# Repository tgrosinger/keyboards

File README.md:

# Keyboards by Tony

Resources and designs for the custom keyboards I have created.

## The Keyboards

### Chrysemys

[Source Files](https://git.sr.ht/~tgrosinger/keyboards/tree/main/item/chrysemys)

A 34-key single-board keyboard created with [Ergogen](https://ergogen.xyz). Powered by a ProMicro-compatible board, such as the nice!nano.

This keyboard is my first attempt at using Ergogen, and my first custom keyboard, so it will likely be rough around the edges. I predict there will be future keyboards listed here which refine the ideas implemented in this board.

### Pseudacris

[Source Files](https://git.sr.ht/~tgrosinger/keyboards/tree/main/item/pseudacris)

A 34-key single-board keyboard created with [Ergogen](https://ergogen.xyz). Powered by an integrated MCU, derived directly from the [nRFMicro](https://github.com/joric/nrfmicro/).

This keyboard is almost identical to Chrysemys, but switches to normal Choc switches, adds hotswap, and moves the switches closer together.

### Future Keyboards

Eventually I would like to build a keyboard which has an integrated trackpoint, trackpad, or trackball. It will likely be based on Pseudacris.

## License

All files in this repository are covered by the GPLv3 license. See the [LICENSE](https://git.sr.ht/~tgrosinger/keyboards/tree/main/item/LICENSE) file for more information.

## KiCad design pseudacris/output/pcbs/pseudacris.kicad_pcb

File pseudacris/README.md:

# Pseudacris

A 34-key single-board keyboard created with [Ergogen](https://ergogen.xyz).

This keyboard is materially extremely similar to Chrysemys, with the intention to change the following:

- Change from Kailh Choc Mini to the normal Kailh Choc switches.
  - I have not been happy with how the mini switches feel to type on. They feels as though they are going to bind up too often and especially make chords more difficult.
  - This will reduce manufacturing costs because the extra cutouts needed for the mini switches requires excess milling time.
- Use hotswap sockets for the switches.
- Move the switches closer together, so there is less of a gap between key caps.
- Use an integrated MCU, based on the nRFMicro rather than a nice!nano.

## Building Firmware

The firmware for this keyboard can be found on my [ZMK fork](https://github.com/tgrosinger/zmk/tree/tgrosinger-keyboards/app/boards/arm/pseudacris). Instructions for building can be found in the readme in that directory.

If you would like to build your own key layout for this keyboard, follow the instruction for [Building from `zmk-config` folder](https://zmk.dev/docs/development/build-flash#building-from-zmk-config-folder).

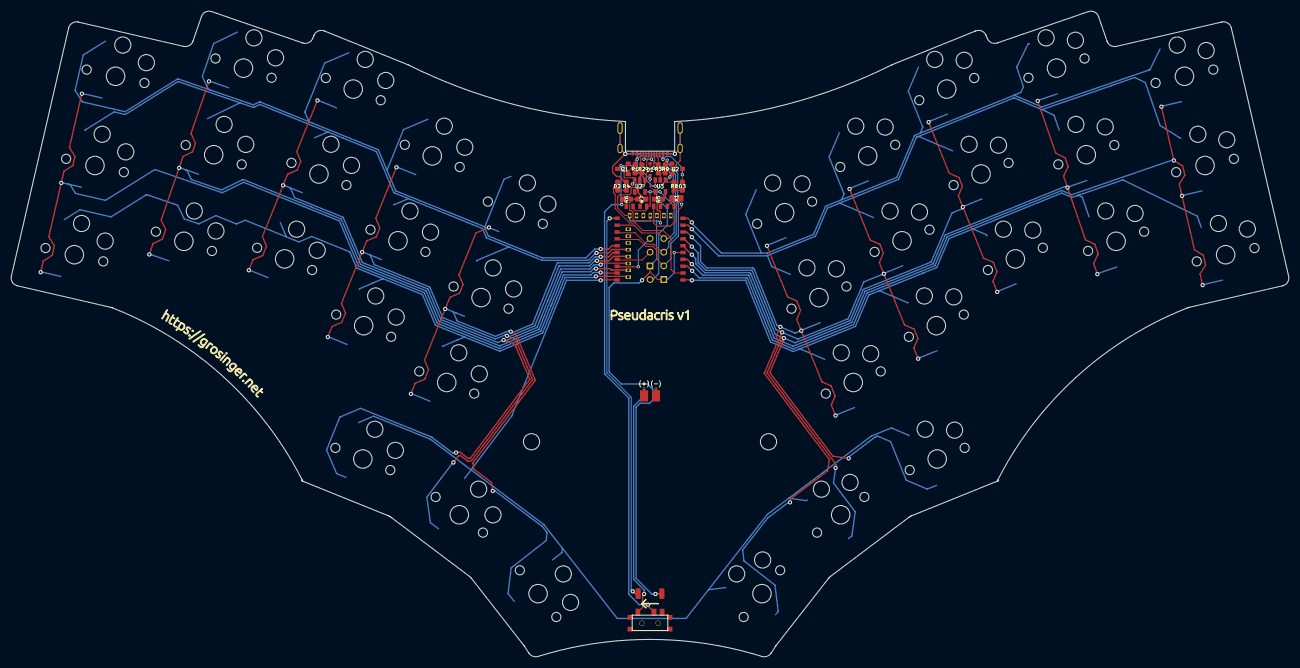
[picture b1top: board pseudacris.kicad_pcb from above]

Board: 2 copper layers, 237.2 x 119.9 mm, 60 parts (0 on the bottom side), 39 nets.

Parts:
B1: Button; TwoLeadButton
BT1: Battery_Cell; BatteryPads
D1: 1N5819; D_SOD-323F
D2: BLUE; LED_0603_1608Metric
D3: RED; LED_0603_1608Metric
J1: USB-C USB 2.0 MC-372; USB-C_C168688
J2: Conn_01x04; connector_swd
J4: Conn_01x04; connector_usb
Q1, Q2: AO3407; SOT-23
R1: 100K; R_0603_1608Metric
R2, R3: 5.1K; R_0603_1608Metric
R4, R8: 1K; R_0603_1608Metric
R5: RPROG; R_0603_1608Metric
R6: 820K; R_0603_1608Metric
R7, R9: 2M; R_0603_1608Metric
S1, S2, S3, S4, S5, S6, S7, S8, S9, S10, S11, S12, S13, S14, S15, S16, S17, S18, S19, S20, S21, S22, S23, S24, S25, S26, S27, S28, S29, S30, S31, S32, S33, S34, S35, S36: PG1350
T1: SPDT_C128955
U1: E73-2G4M08S1C; E73-2G4M08S1C-52840
U2: AP2112K-3.3; SOT-23-5
U3: TP4054; SOT-23-5
X1: 32768kHz; Crystal_SMD_MicroCrystal_CM9V-T1A-2Pin_1.6x1.0mm

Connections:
/P0.00: U1.11 (P0.00/XL1), X1.2
/P0.01: U1.13 (P0.01/XL2), X1.1
/P0.02: S28.2, S29.2, S30.2, S35.2, U1.7 (P0.02/AIN0)
/P0.03: S19.2, S20.2, S21.2, U1.3 (P0.03/AIN1)
/P0.09: S1.2, S2.2, S3.2, U1.41 (P0.09/NFC1)
/P0.10: S16.1, S17.1, S18.1, S34.1, S35.1, S36.1, U1.43 (P0.10/NFC2)
/P0.13: S3.1, S6.1, S9.1, S12.1, S15.1, U1.33 (P0.13)
/P0.22: S2.1, S5.1, S8.1, S11.1, S14.1, U1.34 (P0.22)
/P0.24: S13.2, S14.2, S15.2, S18.2, U1.35 (P0.24)
/P0.28: S22.2, S23.2, S24.2, U1.4 (P0.28/AIN4)
/P0.29: S31.2, S32.2, S33.2, S36.2, U1.8 (P0.29/AIN5)
/P0.30: S21.1, S24.1, S27.1, S30.1, S33.1, U1.10 (P0.30/AIN6)
/P0.31: S20.1, S23.1, S26.1, S29.1, S32.1, U1.9 (P0.31/AIN7)
/P1.00: S10.2, S11.2, S12.2, S17.2, U1.36 (P1.00)
/P1.02: S7.2, S8.2, S9.2, S16.2, U1.38 (P1.02)
/P1.04: S4.2, S5.2, S6.2, U1.40 (P1.04)
/P1.06: S1.1, S4.1, S7.1, S10.1, S13.1, U1.42 (P1.06)
/P1.11: S19.1, S22.1, S25.1, S28.1, S31.1, U1.1 (P1.11)
/P1.13: S25.2, S26.2, S27.2, S34.2, U1.6 (P1.13)
BATT: BT1.1, T1.1
BATTERY_PIN: R6.2, R7.1, U1.18 (P0.04/AIN2)
BLUE_LED: D2.2 (A), U1.2 (P1.10)
CC1: J1.A5 (CC1), R3.1
CC2: J1.B5 (CC2), R2.1
DATA+: J1.A6 (D+), J1.B6 (D+), J4.2, U1.31 (USB_D+)
DATA-: J1.A7 (D-), J1.B7 (D-), J4.3, U1.29 (USB_D-)
GND: B1.2, BT1.2, J1.A1 (GND), J1.S1 (SHIELD), J2.2, J4.1, R1.2, R2.2, R3.2, R4.2, R5.2, R7.2, R9.2, U1.5 (GND), U1.21 (GND), U1.24 (GND), U2.2 (GND), U3.2 (VSS)
unnamed: D1.1 (K), Q1.2 (S), U2.1 (VIN), U2.3 (EN)
unnamed: D2.1 (K), R4.1
unnamed: D3.1 (K), R8.1
unnamed: R5.1, U3.5 (PROG)
unnamed: R8.2, U3.1 (STAT)
POWER_PIN: Q2.1 (G), R9.1, U1.17 (P1.09)
RESET: B1.1, U1.26 (P0.18/RESET)
SWC: J2.4, U1.39 (SWDCLK)
SWD: J2.3, U1.37 (SWDIO)
VBAT: Q1.3 (D), R6.1, T1.2, U3.3 (VBAT)
VBUS: D1.2 (A), D3.2 (A), J1.A4 (VBUS), J4.4, Q1.1 (G), R1.1, U1.27 (VBUS), U3.4 (VDD)
nRF_VDD: J2.1, Q2.2 (S), U1.19 (VDD), U1.23 (VDDH), U2.5 (VOUT)

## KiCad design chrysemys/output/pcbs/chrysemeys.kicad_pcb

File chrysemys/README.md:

# Chrysemys

A 34-key single-board keyboard created with [Ergogen](https://ergogen.xyz).

## Design Goals

- Bluetooth connectivity.
- Single board, with an outward rotation between the two halves for ergonomic comfort.
- Using the ZMK firmware, as it has the best bluetooth support at the moment.
- A focus on keeping the entire keyboard as thin as possible.

## Bill of Materials

- 36 [Kailh Low-Profile Mini Choc Switches (CPG1232)](https://www.aliexpress.com/item/4000277394324.html)
  - Note: These are the "mini" swtiches, which are not compatible with the normal Choc layout.
- 1 package [Kailh Low-Profile Keycaps](https://www.aliexpress.com/item/32979973961.html)
  - Alternatively, the [MBK Choc Keycaps](https://mkultra.click/mbk-choc-keycaps)
- 1 Pro-Micro compatible microcontroller. I recommend one with Bluetooth and an integrated battery charger, such as the [nice!nano](https://nicekeyboards.com/nice-nano/).
- 1 surface mount SPDT sliding switch for the power switch. [LCSC #C128955](https://lcsc.com/product-detail/Slide-Switches_Korean-Hroparts-Elec-K3-1296S-E1_C128955.html) fits the footprint. Alternatively, you can jump the pins on the board and depend on the software standby features.
- 1 surface mount button for the reset switch. [LCSC #C2888943](https://lcsc.com/product-detail/Tactile-Switches_BZCN-TSA010A2010A02_C2888943.html) fits the footprint. This part is optional. You can also jump the reset pin on the MCU with tweezers or bind to a key in QMK.
- 1 301230 LiPo battery such as [this one](https://keyhive.xyz/shop/nicenano)
- Adhesive rubber dome feet

## Center Cover

After use, I have decided to instead place the battery under the nice!nano and omit the center cover. This does leave a hole in the middle of the keyboard, but maybe we just call it a handle.

## Firmware

- [Docs](https://zmk.dev/docs/development/build-flash#building-from-zmk-config-folder) on building firmware using the `zmk-config` from this repo.
  - Note: It still needs to be built from inside the `/app` directory in the ZMK repo.
  - `west build -b nice_nano_v2 -- -DSHIELD=chrysemys -DZMK_CONFIG="/workspaces/zmk-config/config"`

## Inspiration

### GergoPlex

The [GergoPlex](https://www.gboards.ca/product/gergoplex) is a 36 key keyboard which I purchased as a partialy assembled board. The key layout is excellent, however the thumb keys are slightly too far in towards the hands, and the split design results in my keyboard halves wandering away from me, or hard to use on uneven surfaces. I worked around some of these problems by creating a board in which the two halves are nestled in just the right orientation, however that does not help the thumb key issue.

### Hummingbird

The [Hummingbird layout](https://github.com/PJE66/hummingbird), and [Rufous, the Ergogen recreation](https://github.com/jcmkk3/trochilidae/tree/main/rufous) have been a big help in getting me started with Ergogen and building the layout I'm looking for.

## Credits

### Footprints

- Several footprints used in this project were borrowed from [jcmkk3's Trochildae collection](https://github.com/jcmkk3/trochilidae/tree/main/trochilidae.pretty)

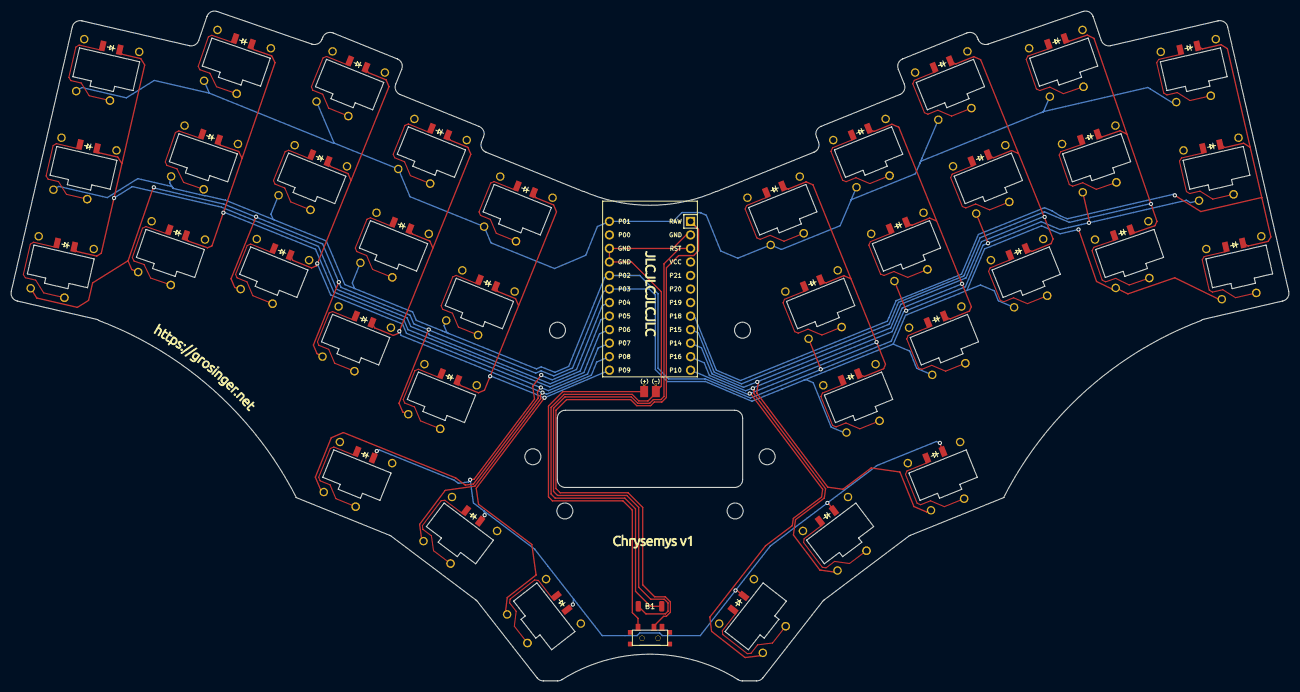
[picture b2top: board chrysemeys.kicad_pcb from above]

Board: 2 copper layers, 240.0 x 125.8 mm, 40 parts (0 on the bottom side), 18 nets.

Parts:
B1: Button; TwoLeadButton
BT1: Battery_Cell; BatteryPads
MCU1: ProMicro
S1, S2, S3, S4, S5, S6, S7, S8, S9, S10, S11, S12, S13, S14, S15, S16, S17, S18, S19, S20, S21, S22, S23, S24, S25, S26, S27, S28, S29, S30, S31, S32, S33, S34, S35, S36: Kailh_PG1232
T1: SPDT_C128955

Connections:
BATT: BT1.1, T1.1
GND: B1.2, BT1.2, MCU1.2, MCU1.15, MCU1.16
P1: MCU1.13, S3.1, S6.1, S9.1, S12.1, S15.1, S21.1, S24.1, S27.1, S30.1, S33.1
P2: MCU1.17, S2.1, S5.1, S8.1, S11.1, S14.1, S20.1, S23.1, S26.1, S29.1, S32.1
P3: MCU1.18, S1.1, S4.1, S7.1, S10.1, S13.1, S19.1, S22.1, S25.1, S28.1, S31.1
P4: MCU1.19, S16.2, S17.2, S18.2, S34.2, S35.2, S36.2
P5: MCU1.20, S1.2, S2.2, S3.2
P6: MCU1.21, S4.2, S5.2, S6.2
P7: MCU1.22, S7.2, S8.2, S9.2, S16.1
P8: MCU1.23, S10.2, S11.2, S12.2, S17.1
P9: MCU1.24, S13.2, S14.2, S15.2, S18.1
P10: MCU1.12, S31.2, S32.2, S33.2, S36.1
P14: MCU1.10, S25.2, S26.2, S27.2, S34.1
P15: MCU1.9, S22.2, S23.2, S24.2
P16: MCU1.11, S28.2, S29.2, S30.2, S35.1
P18: MCU1.8, S19.2, S20.2, S21.2
RAW: MCU1.1, T1.2
RST: B1.1, MCU1.3

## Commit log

2022-04-09 Inital Commit
2022-04-09 Add a license
2022-04-09 Create subdirectory for chrysemys
2022-04-09 Update to readme files
2022-04-12 Initial version of layout
2022-04-12 Closing in on panel layout
2022-04-13 Add radius to center
2022-04-13 Add outline for center cover plate
2022-04-16 Add footprints and nets
    Still missing the MCU and diodes.
2022-04-18 Add diodes to switches
2022-04-19 Add MCU and assign nets to more sane pins
2022-04-19 Add pads for soldering battery connnection
2022-04-19 Add cutout for mounting battery
2022-04-19 Demo cleanup
2022-04-19 Add mounting holes
2022-04-20 Add footprint for chocmini with diode
2022-04-21 Add footprint for mounting hole and battery pads
2022-04-21 Add reset jumper and power switch
2022-04-24 Add new reset button footprint
2022-04-24 Initial routing of PCB
2022-04-24 Add output artifacts
2022-04-24 Add gitignore
2022-04-26 Small pcb tweaks for DRC
2022-04-27 Add artwork
2022-04-27 Update Chrysemys BOM
2022-06-30 Initialize pseudacris as a copy of chrysemys
2022-06-30 Start making updates for pseudacris
2022-06-30 Notes about chrysemys after use
2022-06-30 Continue moving keys closer together
2022-07-04 Finished updating board outline
2022-07-05 Start routing pseudacris
2022-07-06 Refining pcb layout
2022-07-06 Pseudacris v1 sent to manufacturer
2022-07-16 Ignore extra kicad files
2022-07-16 Update readme files
